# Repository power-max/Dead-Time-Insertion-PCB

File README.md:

# Dead Time Insertion PCB

This KiCad PCB module is designed to take a single-ended TTL level square wave signal from some source and create a sort of "complementary output" but with the propagation delay for the rising edge signal delayed significantly more than the falling edge (or the opposite case if the output is inverted). This allows for driving the high and low side of a half bridge to ensure break-before-make condition.

The pinout of the 0.1 pin header has several options.

## Pin 1 (DEADTIME_CTRL)
This pin allows a current source to control the amount of deadtime that this circuit implements. It simply feeds a current mirror. A lower current will allow for a slower discharge of C5 and C6, which concequentally lead to increased the deadtime. The unfortunate side-effect is this also increases the propagation delay for signals propagating throught this block, particularly for changing the state of switching ON the switching element. Perhaps there is a way to beat causality? please let me know!

## Pin 2 (INPUT)
This is the single TTL level square wave input that is to be converted to a complimentary output for the half bridge.

## Pin 3 (INVERT)
Invert output allows the output pins 7 and 8 to be inverted, such as may be required if you are using an inverted input gate driver IC. Set this HIGH if you wish to use inverting FET driver IC.

## Pin 4 (~EN) 
This is just an ENABLE. The outputs are held at whatever the respective LOW state would be depending on the state of Pin 3, ensuring both Hi and Lo side FETs remain OFF.

## Pin 5 (VCC)
power for the circuit. Added an LDO regulator footprint (SOT-89) to the circuit, would recommend an LDO to allow operation down to around 3V depending on output voltage requirements and input voltage range.

## Pin 6 (GND)
GND, RTN, or COM. Whatever you prefer to call it.

## Pin 7 (OUT_L)
This is the output intended for the LO-side switching element gate driver.

## Pin 8 (OUT_H)
This is the output intended for the HI-side switching element gate driver.

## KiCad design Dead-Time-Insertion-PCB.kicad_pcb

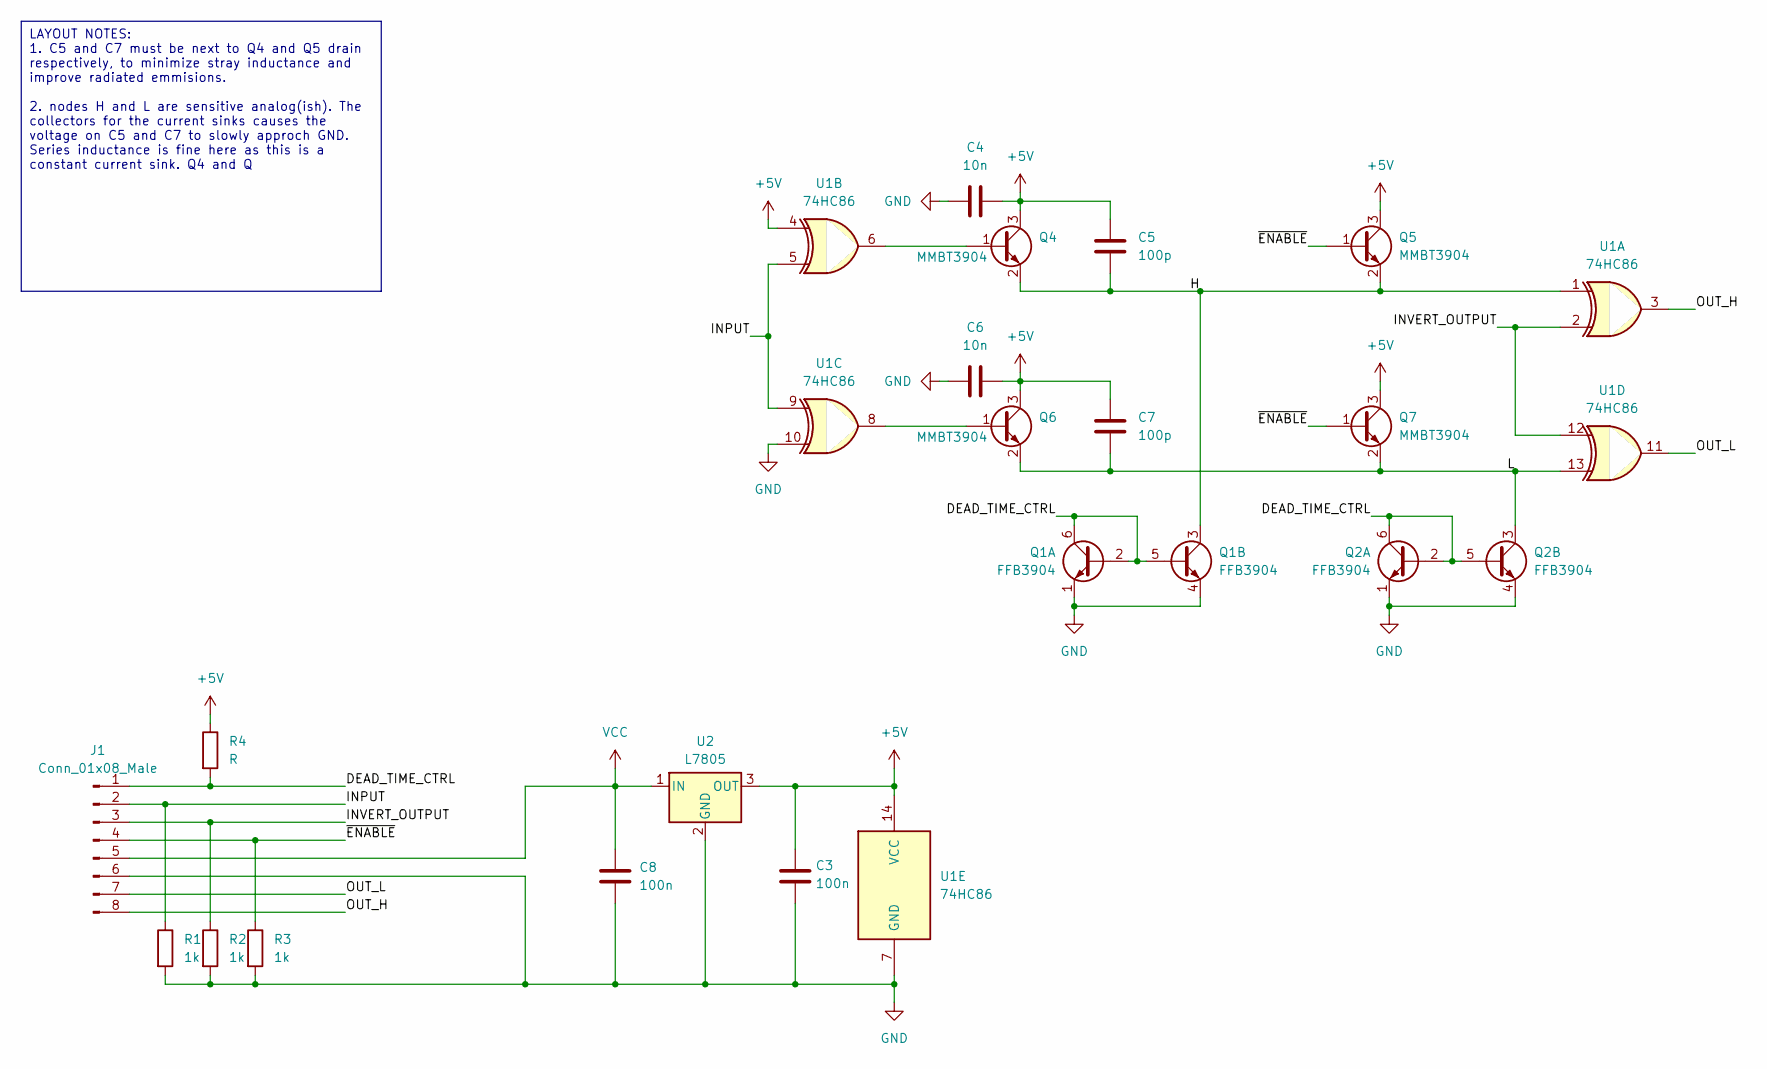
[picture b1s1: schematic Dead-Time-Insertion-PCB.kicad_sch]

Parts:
C3, C8: 100n; C_0603_1608Metric
C4, C6: 10n; C_0603_1608Metric
C5, C7: 100p; C_0603_1608Metric
J1: Conn_01x08_Male; PinHeader_1x08_P2.54mm_Vertical
Q1, Q2: FFB3904; SOT-363_SC-70-6
Q4, Q5, Q6, Q7: MMBT3904; SOT-23
R1, R2, R3: 1k; R_0603_1608Metric
R4: R; R_0603_1608Metric
U1: 74HC86; SOIC-14_3.9x8.7mm_P1.27mm
U2: L7805; SOT-89-3

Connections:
+5V: C3.1, C4.1, C5.1, C6.1, C7.1, Q4.3 (C), Q5.3 (C), Q6.3 (C), Q7.3 (C), R4.1, U1.4, U1.14 (VCC), U2.3 (OUT)
/DEAD_TIME_CTRL: J1.1, Q1.2 (B1), Q1.5 (B2), Q1.6 (C1), Q2.2 (B1), Q2.5 (B2), Q2.6 (C1), R4.2
/H: C5.2, Q1.3 (C2), Q4.2 (E), Q5.2 (E), U1.1
/INPUT: J1.2, R1.1, U1.5, U1.9
/INVERT_OUTPUT: J1.3, R2.1, U1.2, U1.12
/L: C7.2, Q2.3 (C2), Q6.2 (E), Q7.2 (E), U1.13
/OUT_H: J1.8, U1.3
/OUT_L: J1.7, U1.11
/~ENABLE: J1.4, Q5.1 (B), Q7.1 (B), R3.1
GND: C3.2, C4.2, C6.2, C8.2, J1.6, Q1.1 (E1), Q1.4 (E2), Q2.1 (E1), Q2.4 (E2), R1.2, R2.2, R3.2, U1.7 (GND), U1.10, U2.2 (GND)
unnamed: Q4.1 (B), U1.6
unnamed: Q6.1 (B), U1.8
VCC: C8.1, J1.5, U2.1 (IN)

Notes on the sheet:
LAYOUT NOTES: 1. C5 and C7 must be next to Q4 and Q5 drain respectively, to minimize stray inductance and improve radiated emmisions. 2. nodes H and L are sensitive analog(ish). The collectors for the current sinks causes the voltage on C5 and C7 to slowly approch GND. Series inductance is fine her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

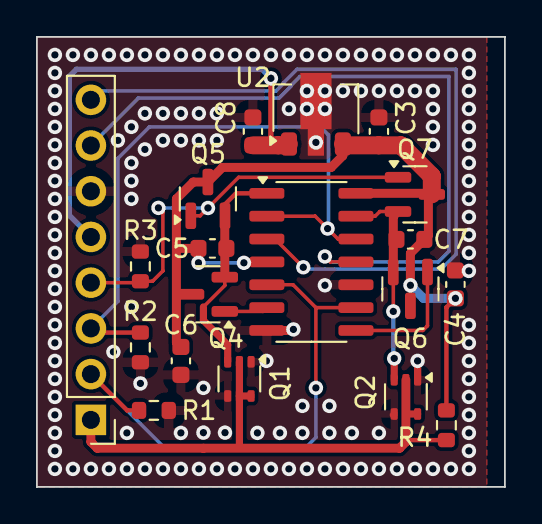
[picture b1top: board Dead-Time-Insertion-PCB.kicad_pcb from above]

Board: 2 copper layers, 26.0 x 25.0 mm, 19 parts (0 on the bottom side), 13 nets.

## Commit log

2022-08-12 added README.md and .gitignore
2022-08-12 Added PCB Files
2022-08-12 Update README.md
    updated README, added additional details, fixed formatting
2024-11-10 added voltage regulator so I don't blow this board up with 12V
2024-11-10 Update README.md
    updated Pin 5 description to reflect update to PCB
2024-11-10 Update .gitignore
    Added rule for ignoring zip files since often the /gerbers file (containing the gerbers and drill file) is compressed for upload to a PCB manufacturing house.
2024-11-10 Delete gerbers.zip
    zip file is entirely redundant with the /gerbers folder.
2024-11-10 addressed parasitic oscillations by adding pulldown/pullup resistors, overhauling the PCB layout to reduce the footprint of sensitive nodes, took great care to avoid cross coupling of input and outpu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
2024-11-10 forgot to update the gerbers
2024-11-10 Update .gitignore
    add ignore any file starting with ~ (KiCAD uses new temp files??)
2024-11-10 cleanup
